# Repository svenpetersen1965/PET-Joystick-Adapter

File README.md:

# PET-Joystick-Adapter
A C64/VIC-20/Atari Joystick Adapter for the Commodore PET. It supports the Coyote Electronics pin configuration (two joysticks) and the space invader/break put style pin configuration (left, right, fire), found on zimmers.net (https://www.zimmers.net/anonftp/pub/cbm/pet/games/english/joy/index.html).

The Coyote Electronics pin configuration is also called "PET User port adapter" in the VICE emulator, so it is expected to be wide spread. Space Invader + is the completed pin configuration of the previously mentioned games and can also be found on the "stupid PET tricks" adapter. Hence the name. 
All joystick games found in the previously mention source could be played with this joystick adapter.

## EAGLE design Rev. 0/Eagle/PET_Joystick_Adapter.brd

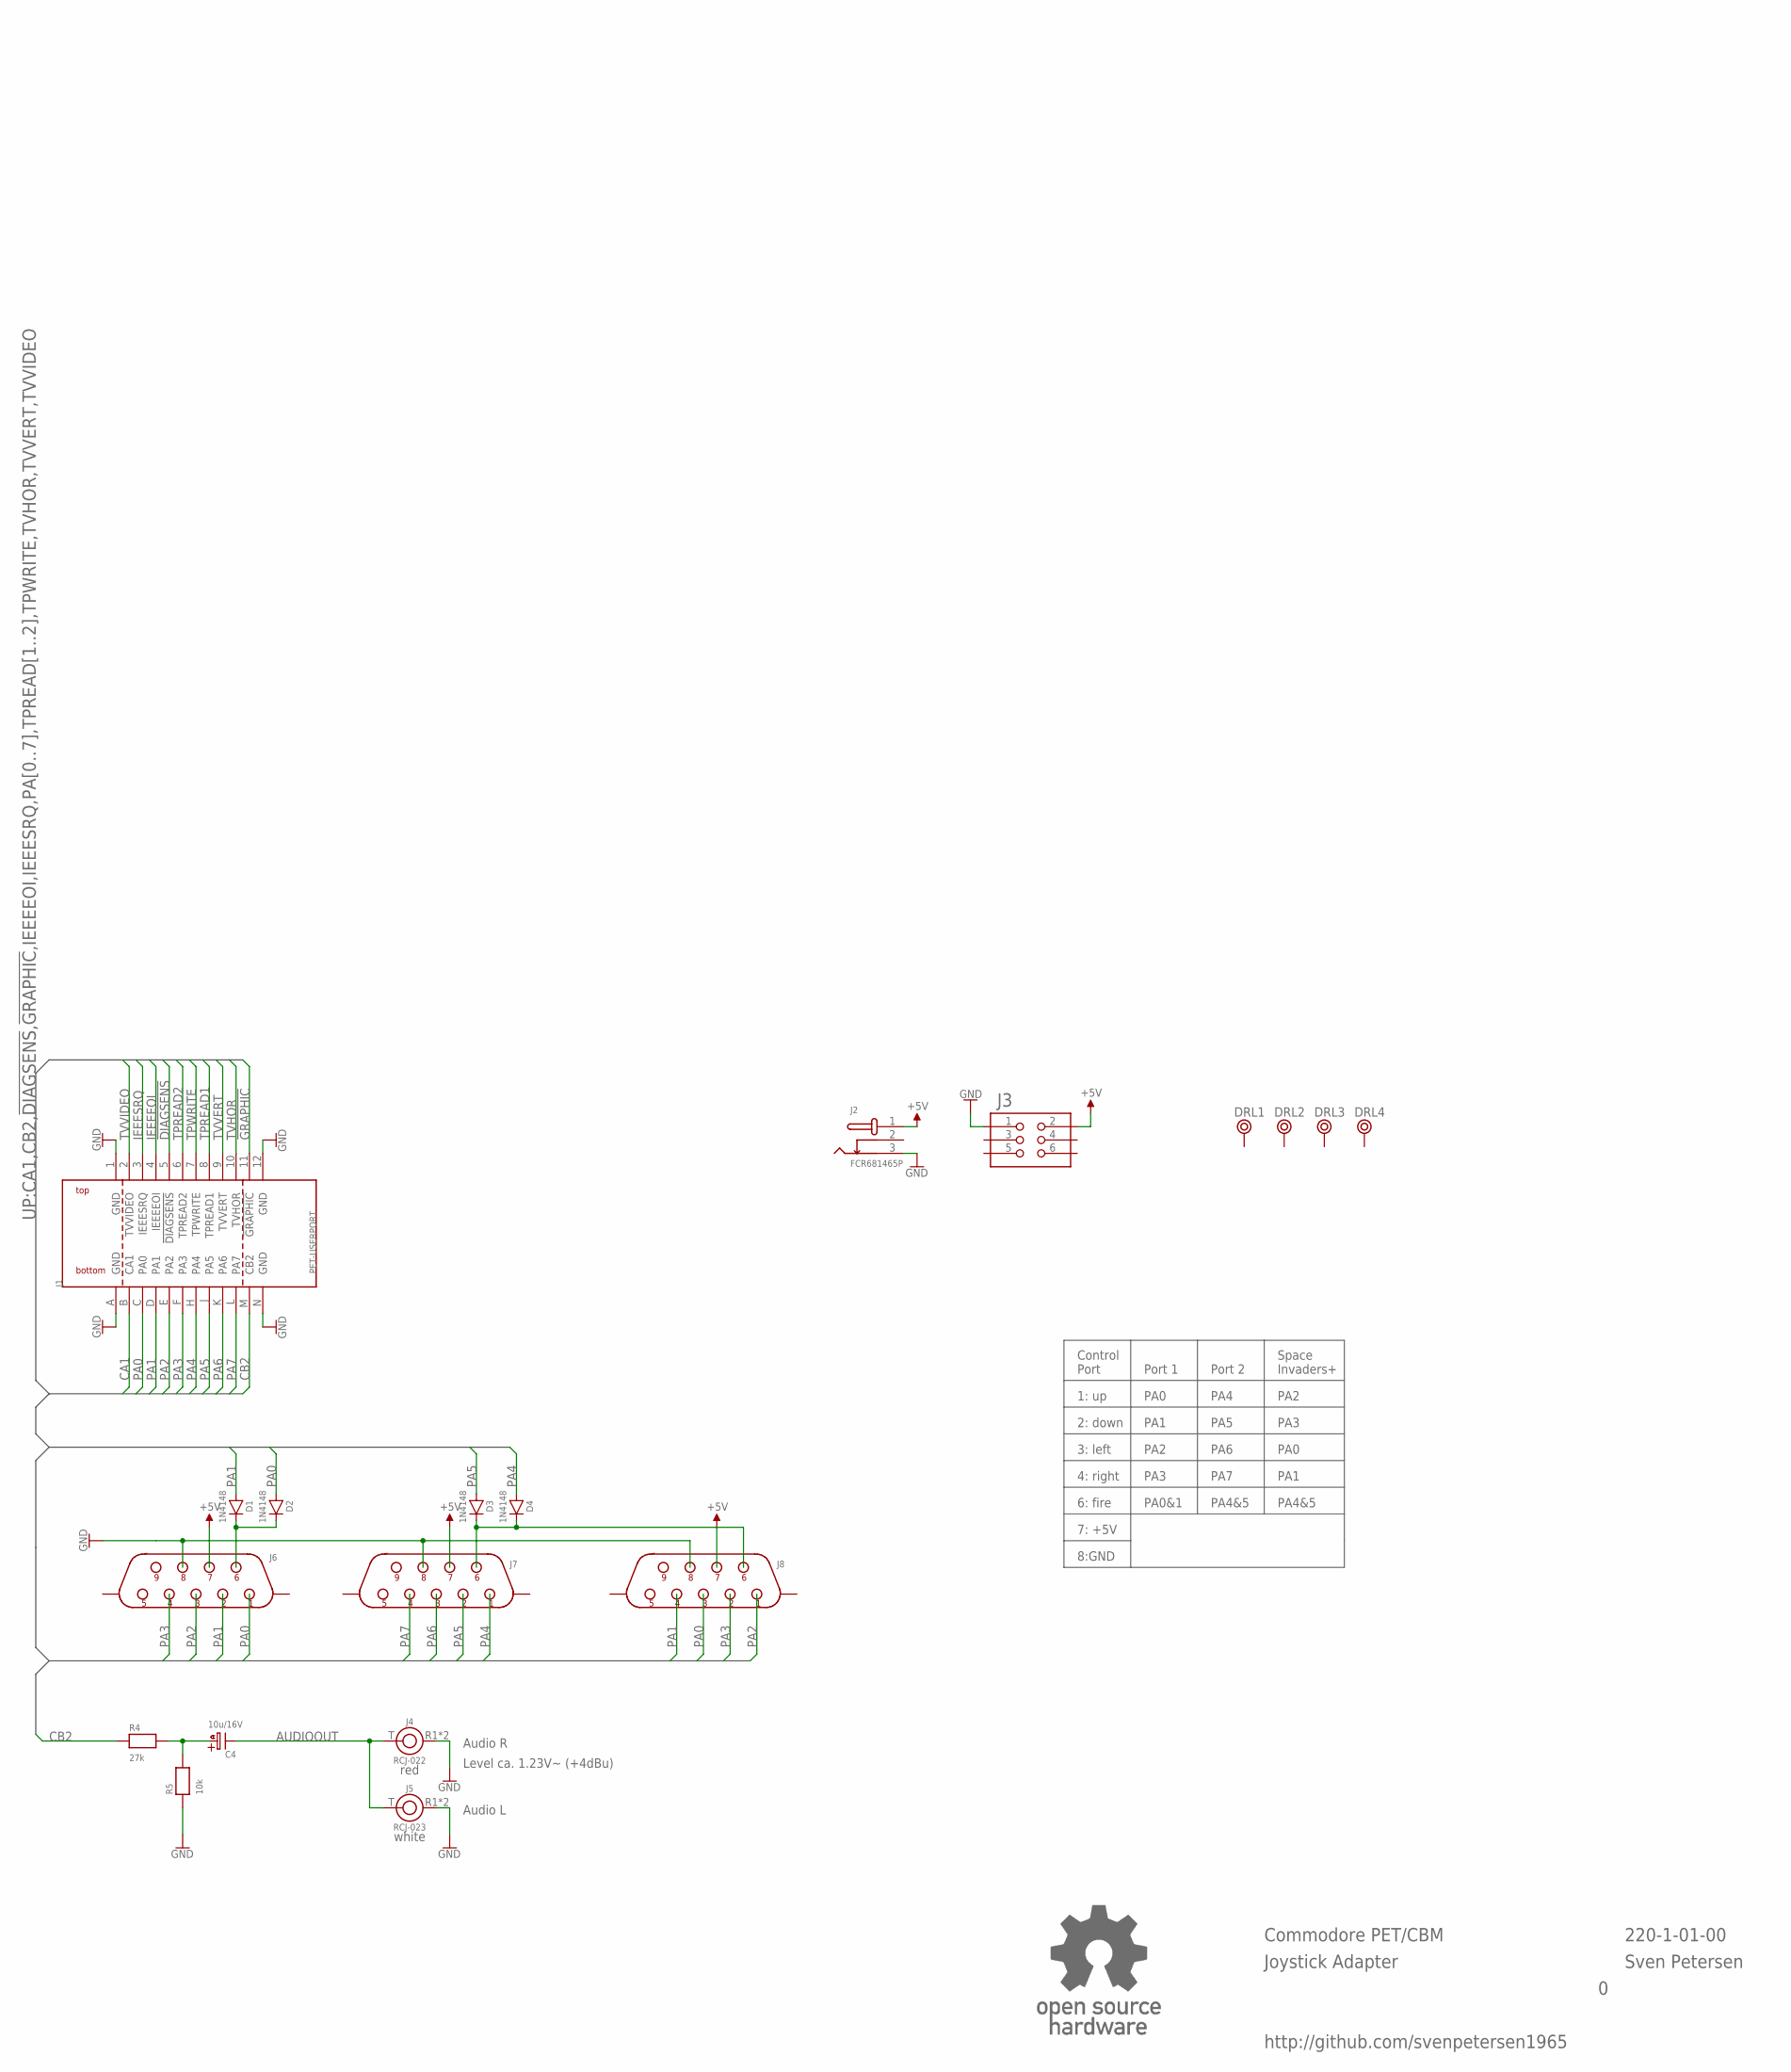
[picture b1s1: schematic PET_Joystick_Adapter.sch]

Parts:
C4: 10u/16V; C5,0/2,0
D1, D2, D3, D4: 1N4148; DO-35/3
DRL1, DRL2, DRL3, DRL4: BOHR3,5
J1: PET-USERPORT; USERPORT
J2: FCR681465P
J3: 2X03WV
J4: RCJ-022; RCJ-02X
J5: RCJ-023; RCJ-02X
J6, J7: DS09M-H-CL; DS9M-H
J8: DS09M-V-CL; DS09M-V
R4: 27k; R-10
R5: 10k; R-10
U$2: OPEN_SOURCE_HW; OPENHW

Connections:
!DIAGSENS: J1.5 (!DIAGSENS)
!GRAPHIC: J1.11 (!GRAPHIC)
+5V: J2.1, J3.2, J6.7, J7.7, J8.7
AUDIOOUT: C4.K (-), J4.T, J5.T
CA1: J1.B (CA1)
CB2: J1.M (CB2), R4.1
GND: J1.1 (GND), J1.12 (GND), J1.A (GND), J1.N (GND), J2.3, J3.1, J4.R1 (R), J4.R2 (R), J5.R1 (R), J5.R2 (R), J6.8, J7.8, J8.8, R5.1
IEEEEOI: J1.4 (IEEEEOI)
IEEESRQ: J1.3 (IEEESRQ)
unnamed: C4.A (+), R4.2, R5.2
unnamed: D1.K, D2.K, J6.6
unnamed: D3.K, D4.K, J7.6, J8.6
PA0: D2.A, J1.C (PA0), J6.1, J8.3
PA1: D1.A, J1.D (PA1), J6.2, J8.4
PA2: J1.E (PA2), J6.3, J8.1
PA3: J1.F (PA3), J6.4, J8.2
PA4: D4.A, J1.H (PA4), J7.1
PA5: D3.A, J1.J (PA5), J7.2
PA6: J1.K (PA6), J7.3
PA7: J1.L (PA7), J7.4
TPREAD1: J1.8 (TPREAD1)
TPREAD2: J1.6 (TPREAD2)
TPWRITE: J1.7 (TPWRITE)
TVHOR: J1.10 (TVHOR)
TVVERT: J1.9 (TVVERT)
TVVIDEO: J1.2 (TVVIDEO)

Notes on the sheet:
http://github.com/svenpetersen1965
Commodore PET/CBM
Joystick Adapter
Sven Petersen
220-1-01-00
red
white
Audio R
Audio L
Level ca. 1.23V~ (+4dBu)
1: up
2: down
3: left
4: right
6: fire
7: +5V
8:GND
Control Port
Port 1
Port 2
Space Invaders+
PA4&5
PA0
PA1
PA2
PA3
PA4
PA5
PA6
PA7
PA0&1

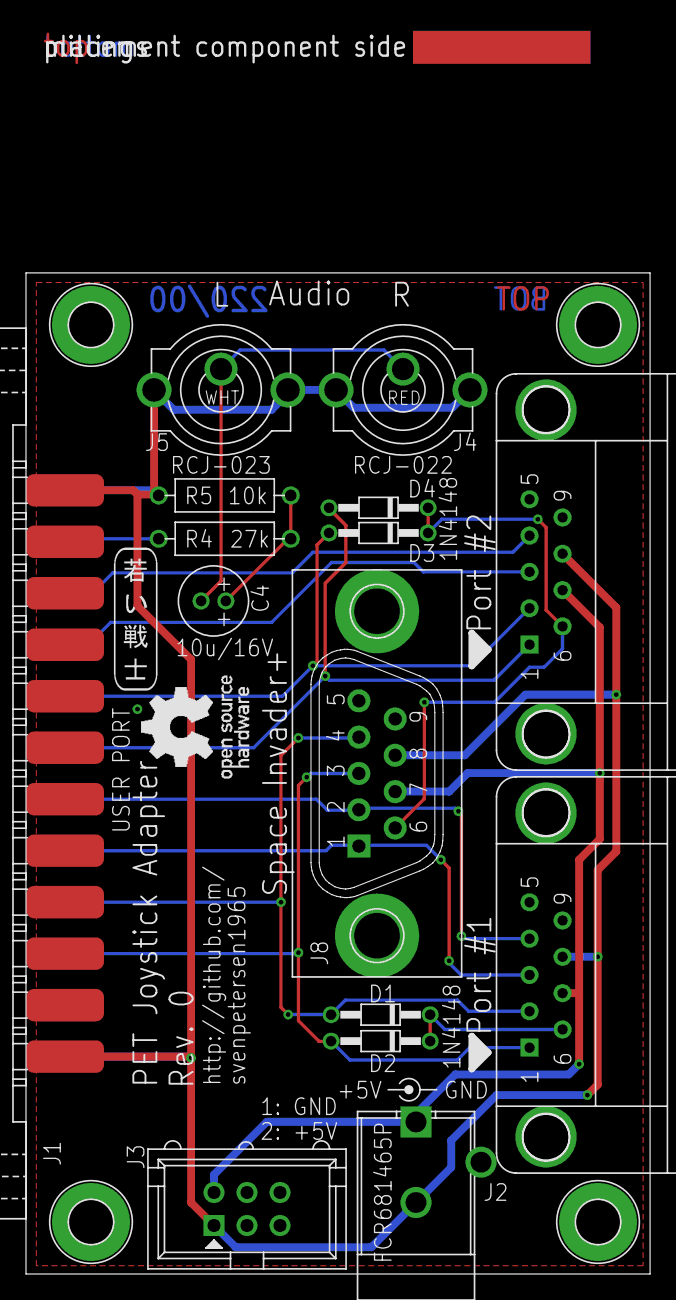
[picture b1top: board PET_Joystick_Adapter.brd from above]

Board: 2 copper layers, 48.0 x 77.0 mm, 23 parts (0 on the bottom side), 15 nets.

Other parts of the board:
U$11: 2LAYER
U$22: PCB-TITLE/
U$26: SVEN_TAG

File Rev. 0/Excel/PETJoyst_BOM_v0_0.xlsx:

Commodore PET Joystick Adapter Rev. 0
Bill of Material Rev. 0.0
Pos. | Qty | Value | Footprint | Ref.-No. | Comment
1 | 1 | 220-2-01-00 | 2 Layer | PCB Rev. 0 | 2 layer, Cu 35µ, HASL, 48.0mm x 77.0mm, 1.6mm FR4
2 | 1 | 2x3 box header, 2.54mm | 2X03WV | J3 | e.g. Reichelt WSL 6G. Option: Power from tape
3 | 2 | Dsub, 9p, male, horizontal | DS9M-H | J6, J7 | e.g. Reichelt BKL 10120037
4 | 1 | Dsub, 9p, male, vertical | DS09M-V | J8 | e.g. Reichelt D-SUB ST 09P
5 | 1 | 10k | R-10 | R5 | 1/4W, 1% or better
6 | 1 | 10u/16V | C5,0/2,0 | C4 | aluminum electrolytic, Æ5.0mm/pitch 2.0mm 105°C, l=11mm, e.G. Reichelt RD1C106M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
7 | 4 | 1N4148 | D1, D2, D3, D4 |  | standard silicon diode
8 | 1 | 27k | R-10 | R4 | 1/4W, 1% or better. 27k for -4dBU or 62k for -10dBU audio level.
9 | 1 | FCR681465P | FCR681465P | J2 | Cliff. 2,5mm/5.5mm barrel connector. E.g. Reichelt CLIFF FCR681465P Option: ext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
10 | 1 | Edge connector, 2x12, 3.96mm | USERPORT | J1 | edge connector, C64 user port, Ali Express, "series 805" or other
11 | 1 | RCJ-022 | RCJ-02X | J4 | CUI Inc., RCA jack, vertical, red. Mouser: 490-RCJ-022, Digikey: CP-1407-ND. Al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
12 | 1 | RCJ-023 | RCJ-02X | J5 | CUI Inc., RCA jack, vertical, white. Mouser: 490-RCJ-023, Digikey: CP-1408-ND. 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

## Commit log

2026-01-16 Initial Upload
2026-01-16 README.md aktualisieren
